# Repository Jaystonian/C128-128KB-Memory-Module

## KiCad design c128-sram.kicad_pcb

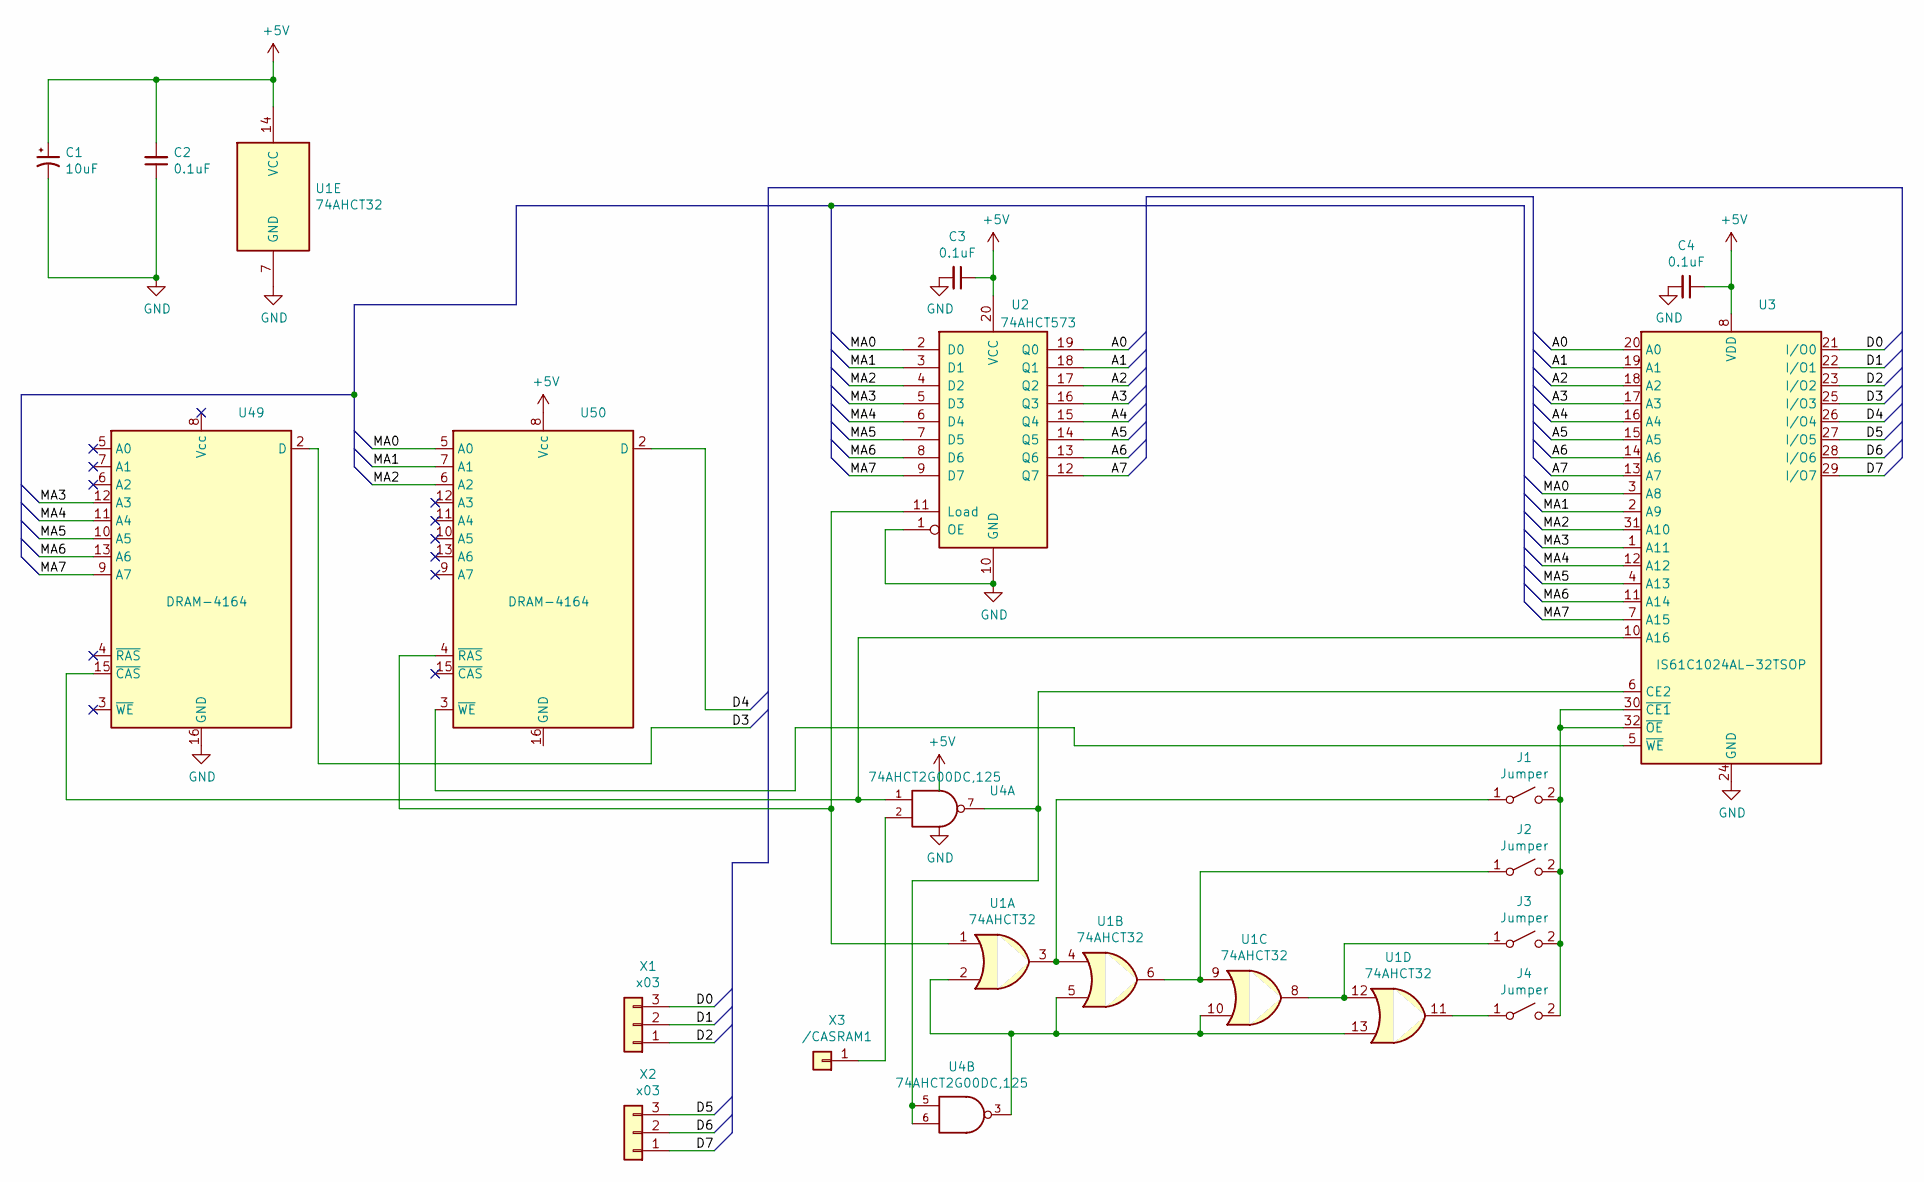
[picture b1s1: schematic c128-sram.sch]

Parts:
C1: 10uF; CP_Radial_D4.0mm_P2.00mm
C2, C3, C4: 0.1uF; C_Disc_D3.0mm_W1.6mm_P2.50mm
J1, J2, J3, J4: Jumper; SolderJumper-2_P1.3mm_Open_RoundedPad1.0x1.5mm
U1: 74AHCT32; SOIC-14_3.9x8.7mm_P1.27mm
U2: 74AHCT573; SO-20_12.8x7.5mm_P1.27mm
U3: IS61C1024AL-32TSOP; TSOP-I-32_18.4x8mm_P0.5mm
U4: 74AHCT2G00DC,125; VSSOP-8_2.4x2.1mm_P0.5mm
U49: DRAM-4164; DIP-16_W7.62mm-DRAM4164L
U50: DRAM-4164; DIP-16_W7.62mm-DRAM4164R
X1, X2: x03; PinHeader_1x03_P2.54mm_Vertical
X3: /CASRAM1; PinHeader_1x01_P2.54mm_Vertical

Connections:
+5V: C1.1, C2.2, C3.1, C4.1, U1.14 (VCC), U2.20 (VCC), U3.8 (VDD), U4.8 (VCC), U50.8 (Vcc)
/A0: U2.19 (Q0), U3.20 (A0)
/A1: U2.18 (Q1), U3.19 (A1)
/A2: U2.17 (Q2), U3.18 (A2)
/A3: U2.16 (Q3), U3.17 (A3)
/A4: U2.15 (Q4), U3.16 (A4)
/A5: U2.14 (Q5), U3.15 (A5)
/A6: U2.13 (Q6), U3.14 (A6)
/A7: U2.12 (Q7), U3.13 (A7)
/D0: U3.21 (I/O0), X1.3
/D1: U3.22 (I/O1), X1.2
/D2: U3.23 (I/O2), X1.1
/D3: U3.25 (I/O3), U49.2 (D)
/D4: U3.26 (I/O4), U50.2 (D)
/D5: U3.27 (I/O5), X2.3
/D6: U3.28 (I/O6), X2.2
/D7: U3.29 (I/O7), X2.1
/MA0: U2.2 (D0), U3.3 (A8), U50.5 (A0)
/MA1: U2.3 (D1), U3.2 (A9), U50.7 (A1)
/MA2: U2.4 (D2), U3.31 (A10), U50.6 (A2)
/MA3: U2.5 (D3), U3.1 (A11), U49.12 (A3)
/MA4: U2.6 (D4), U3.12 (A12), U49.11 (A4)
/MA5: U2.7 (D5), U3.4 (A13), U49.10 (A5)
/MA6: U2.8 (D6), U3.11 (A14), U49.13 (A6)
/MA7: U2.9 (D7), U3.7 (A15), U49.9 (A7)
GND: C1.2, C2.1, C3.2, C4.2, U1.7 (GND), U2.1 (OE), U2.10 (GND), U3.24 (GND), U4.4 (GND), U49.16 (GND)
unnamed: J1.1 (A), U1.3, U1.4
unnamed: J1.2 (B), J2.2 (B), J3.2 (B), J4.2 (B), U3.30 (~CE1), U3.32 (~OE)
unnamed: J2.1 (A), U1.6, U1.9
unnamed: J3.1 (A), U1.8, U1.12
unnamed: J4.1 (A), U1.11
unnamed: U1.1, U2.11 (Load), U50.4 (~RAS)
unnamed: U1.2, U1.5, U1.10, U1.13, U4.3
unnamed: U3.5 (~WE), U50.3 (~WE~)
unnamed: U3.6 (CE2), U4.5, U4.6, U4.7
unnamed: U3.10 (A16), U4.1, U49.15 (~CAS)
unnamed: U4.2, X3.1

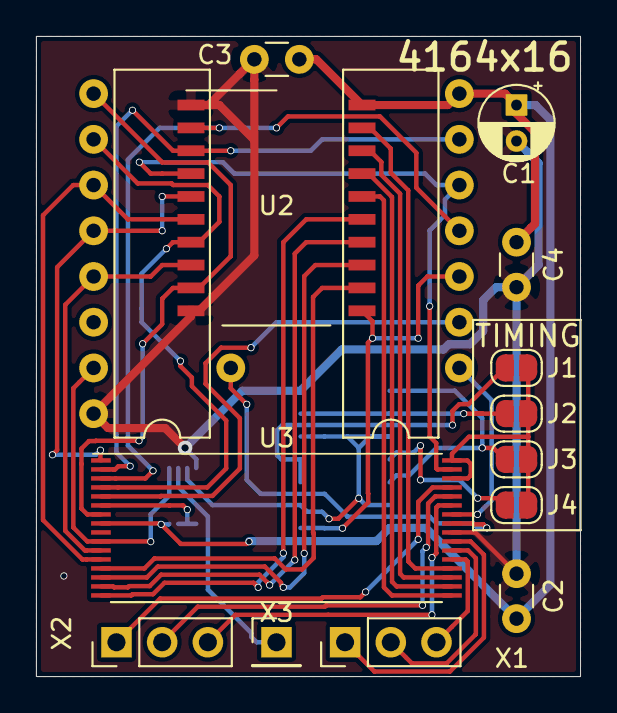
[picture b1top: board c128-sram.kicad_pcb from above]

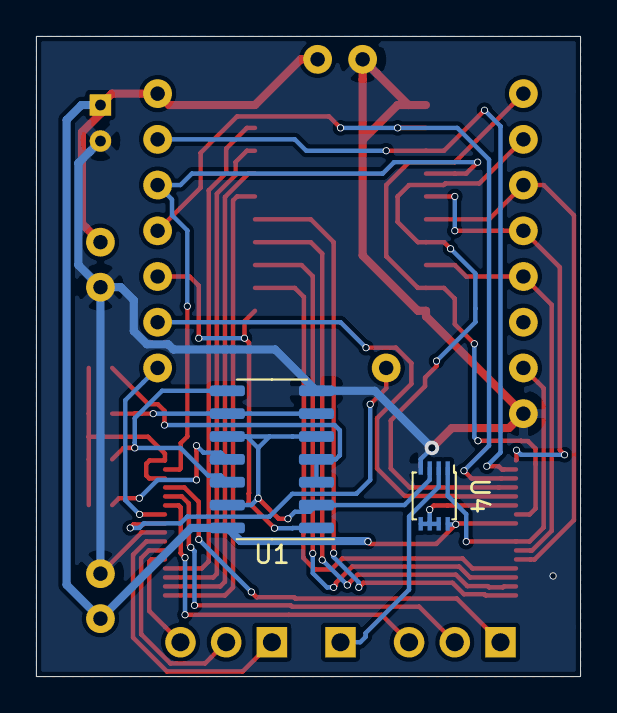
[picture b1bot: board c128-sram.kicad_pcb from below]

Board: 2 copper layers, 30.2 x 35.6 mm, 17 parts (2 on the bottom side), 37 nets.
